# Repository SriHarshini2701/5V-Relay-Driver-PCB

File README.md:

# 5V-Relay-Driver-PCB

## Project Overview

This project implements a 5V MCU-controlled relay driver PCB designed in KiCad for switching a 12V DC motor load. The relay coil is driven using a P2N2222A NPN transistor operating in saturation mode. A flyback diode is included across the relay coil to suppress inductive voltage spikes and protect the transistor during turn-off.

The project covers the complete hardware design flow including schematic capture, LTspice simulation, PCB layout, ERC/DRC verification, BOM generation, and manufacturing file generation.

---

## Design Specifications

| Parameter           | Value                   |
| ------------------- | ----------------------- |
| MCU Control Voltage | 5 V                     |
| Relay               | Omron G5LE-1 DC5        |
| Relay Coil Voltage  | 5 V                     |
| Relay Coil Current  | 79.4 mA                 |
| Load Voltage        | 12 V DC                 |
| Load Type           | DC Motor                |
| Switching Device    | P2N2222A NPN Transistor |
| Base Resistor       | 1 kΩ                    |
| Protection          | Flyback Diode           |
| PCB Layers          | 2-Layer PCB             |
| Design Tool         | KiCad                   |
| Simulation Tool     | LTspice                 |

---

## Circuit Operation

The MCU output drives the base of a P2N2222A transistor through a 560Ω resistor. When the MCU output goes HIGH, the transistor enters saturation and energizes the relay coil. The relay contacts then connect the 12V supply to the motor load.

A flyback diode connected across the relay coil suppresses the back-EMF generated when the relay is switched OFF, protecting the transistor from high-voltage transients.

---

## Schematic

*Relay driver schematic showing MCU interface, transistor driver stage, relay coil protection diode, status LED, and motor switching contacts.*

---

## PCB Layout

### Top Layer

*Top layer PCB layout generated in KiCad.*

### 3D View

*3D rendering of the completed relay driver PCB.*

---

## LTspice Simulation Results

### Relay Coil Current Verification

*Measured relay coil current ≈ 77.8 mA, validating proper energization of the Omron G5LE-1 relay.*

---

### Base and Collector Current Verification

*Base current ≈ 7.38 mA and collector current ≈ 77.8 mA verify correct transistor drive and base resistor selection.*

---

### Flyback Diode Verification

*Flyback diode suppresses the inductive voltage spike generated by the relay coil during turn-off, protecting the switching transistor.*

---

## Design Verification

### Electrical Rules Check (ERC)

✔ No ERC errors

### Design Rules Check (DRC)

✔ No DRC violations

### Manufacturing Outputs Generated

✔ Gerber Files

✔ Drill Files

✔ Bill of Materials (BOM)

---

## Key Skills Demonstrated

* Schematic Capture
* Relay Driver Design
* Transistor Switching Circuits
* Component Selection
* LTspice Simulation
* PCB Layout Design
* ERC and DRC Verification
* BOM Generation
* Gerber Generation
* Hardware Design Documentation
* Manufacturing Output Preparation

---

## Author

Sri Harshini N

[LinkedIn](https://www.linkedin.com/in/sri-harshini-n-439b87212/) | [GitHub](https://github.com/SriHarshini2701)

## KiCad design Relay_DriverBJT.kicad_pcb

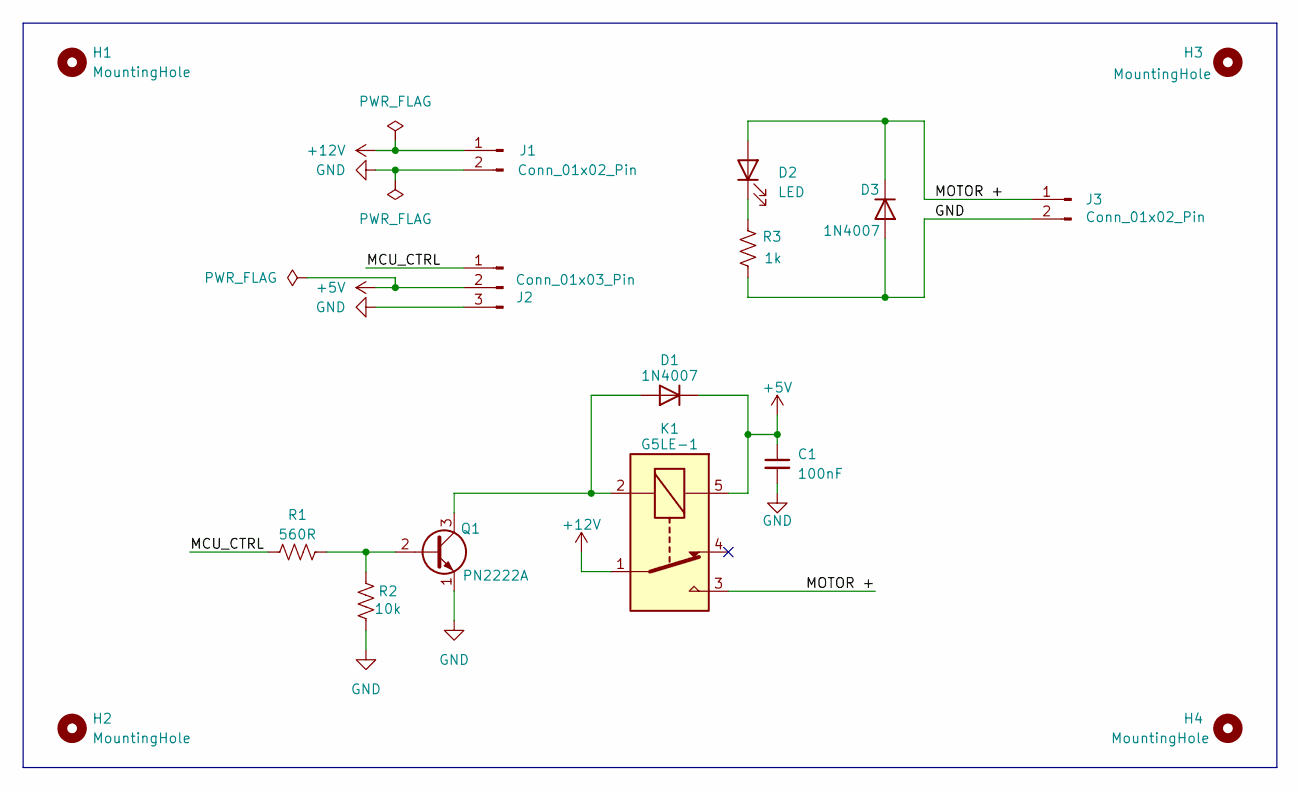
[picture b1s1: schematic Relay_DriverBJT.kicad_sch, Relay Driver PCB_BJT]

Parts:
C1: 100nF; C_0805_2012Metric
D1, D3: 1N4007; D_DO-41_SOD81_P10.16mm_Horizontal
D2: LED; LED_0805_2012Metric
H1, H2, H3, H4: MountingHole; MountingHole_3.2mm_M3
J1, J3: Conn_01x02_Pin; TerminalBlock_bornier-2_P5.08mm
J2: Conn_01x03_Pin; TerminalBlock_bornier-3_P5.08mm
K1: G5LE-1; Relay_SPDT_Omron-G5LE-1
Q1: PN2222A; TO-92_Inline
R1: 560R; R_0805_2012Metric
R2: 10k; R_0805_2012Metric
R3: 1k; R_0805_2012Metric

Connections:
+5V: C1.1, D1.1 (K), J2.2, K1.5
+12V: J1.1, K1.1
/MCU_CTRL: J2.1, R1.1
/MOTOR +: D2.2 (A), D3.1 (K), J3.1, K1.3
GND: C1.2, D3.2 (A), J1.2, J2.3, J3.2, Q1.1 (E), R2.2, R3.2
unnamed: D1.2 (A), K1.2, Q1.3 (C)
unnamed: D2.1 (K), R3.1
unnamed: Q1.2 (B), R1.2, R2.1

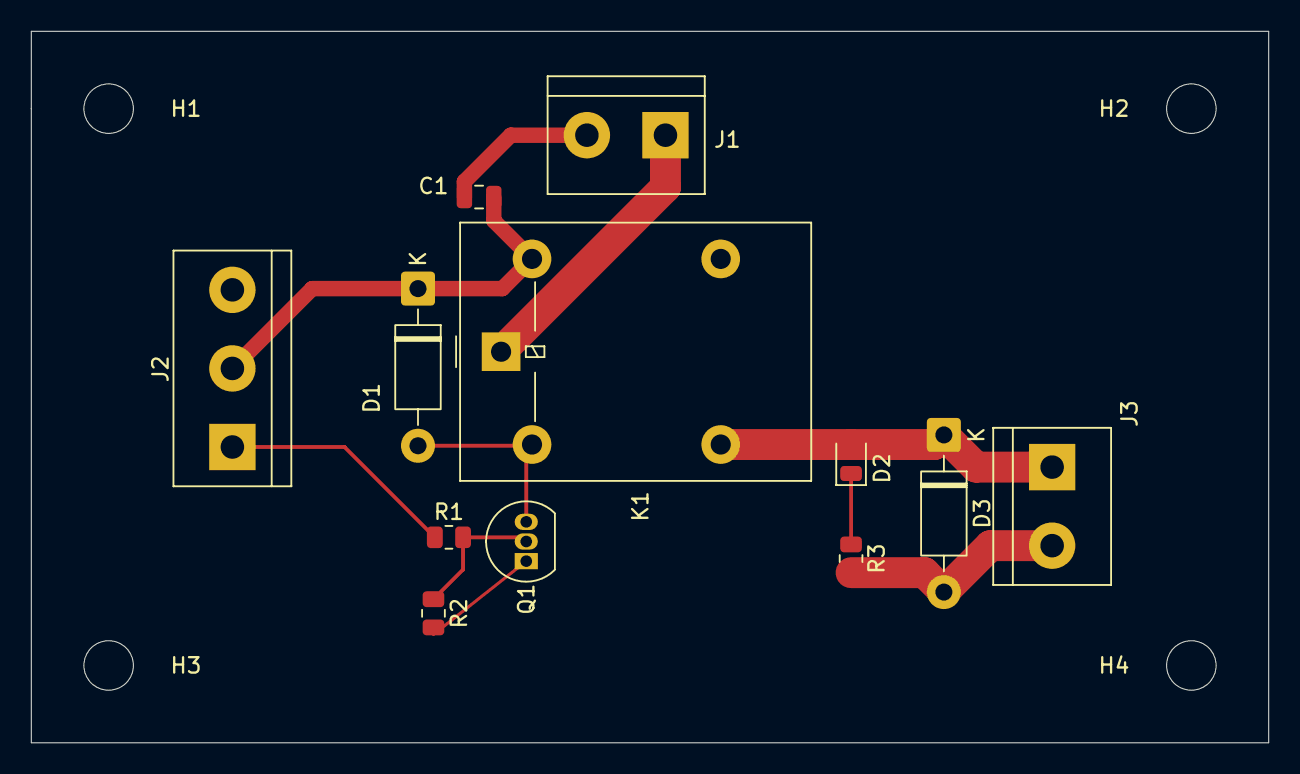
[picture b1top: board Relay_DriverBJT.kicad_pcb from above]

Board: 2 copper layers, 80.0 x 46.0 mm, 16 parts (0 on the bottom side), 8 nets.
